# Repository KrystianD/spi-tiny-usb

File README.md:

spi-tiny-usb
============

SPI interface adapter over USB with Linux kernel module.

NOTE: you need to set your custom VID/PID pair for USB device descriptor as I do not provide any.

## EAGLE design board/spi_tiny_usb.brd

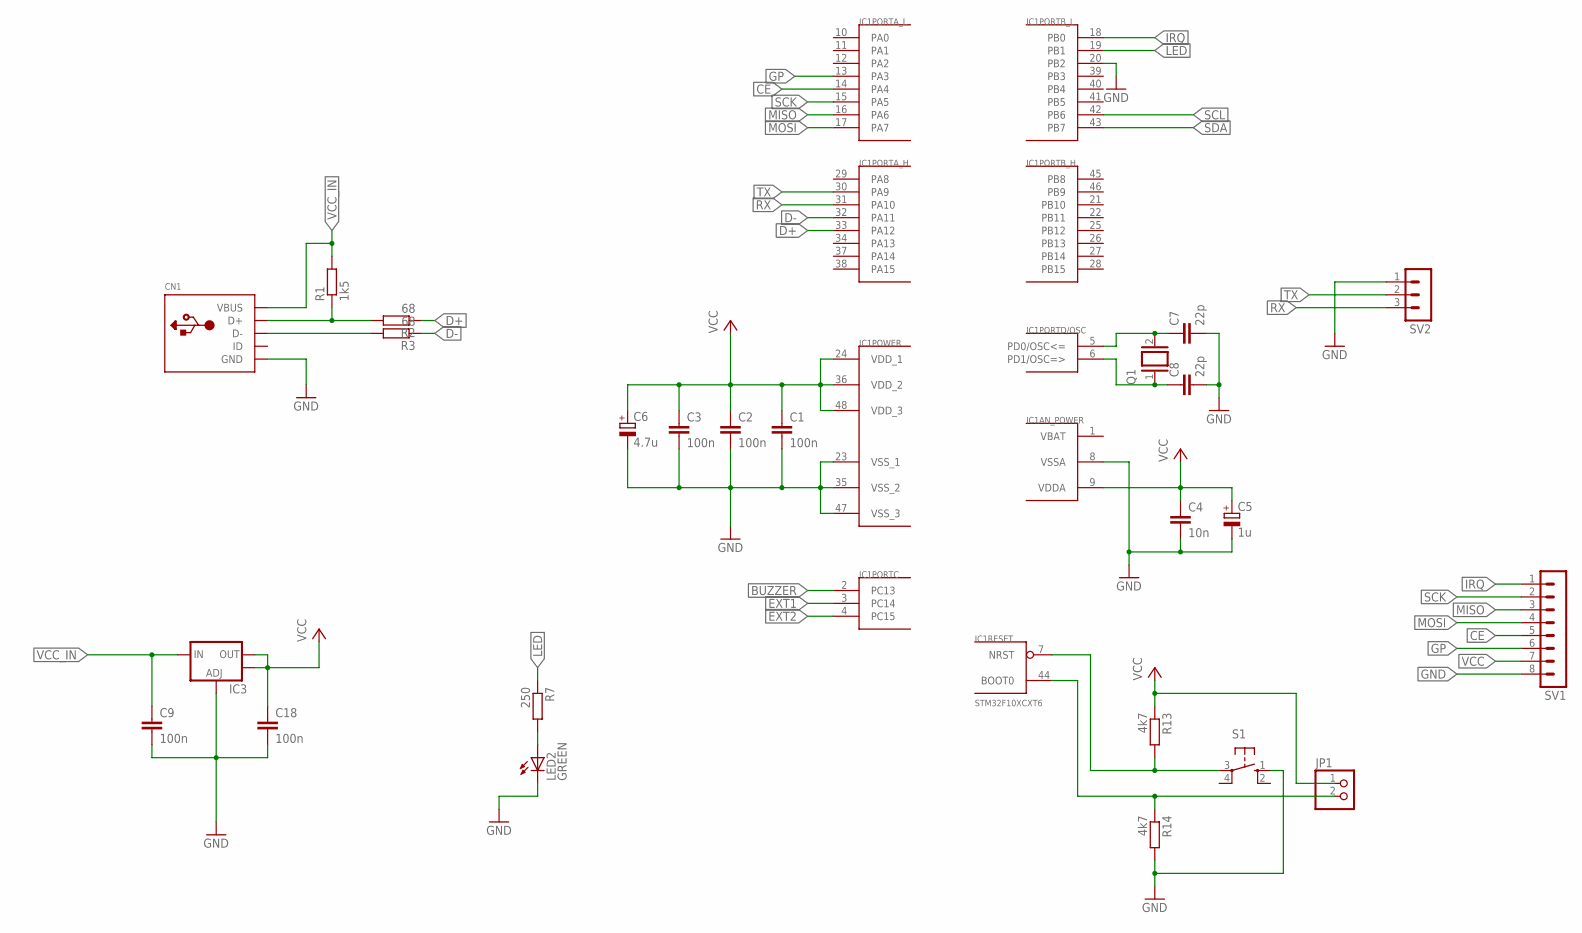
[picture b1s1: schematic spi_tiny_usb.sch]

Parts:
C1, C2, C3, C9, C18: 100n; C0805
C4: 10n; C0805
C5: 1u; 153CLV-0505
C6: 4.7u; 153CLV-0505
C7, C8: 22p; C0805
CN1: USBMINIB; USB-MINIB
IC1: STM32F10XCXT6; TQFP48
IC3: V_REG_LM1117SOT223; SOT223
JP1: PINHD-1X2; 1X02
LED2: GREEN; CHIPLED_0805
Q1: XTAL/S; QS
R1: 1k5; M1206
R2, R3: 68; M0805
R7: 250; R0805
R13: 4k7; R0805
R14: 4k7; R1206
S1: 10-XX; B3F-10XX
SV1: MA08-1
SV2: MA03-1

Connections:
BUZZER: IC1.2 (PC13)
CE: IC1.14 (PA4), SV1.5
D+: IC1.33 (PA12), R2.1
D-: IC1.32 (PA11), R3.1
EXT1: IC1.3 (PC14)
EXT2: IC1.4 (PC15)
GND: C1.2, C2.2, C3.2, C4.2, C5.-, C6.-, C7.2, C8.2, C9.2, C18.2, CN1.GND, IC1.8 (VSSA), IC1.20 (PB2), IC1.23 (VSS_1), IC1.35 (VSS_2), IC1.47 (VSS_3), IC3.1 (ADJ), LED2.C, R14.2, S1.1 (S), SV1.8, SV2.1
GP: IC1.13 (PA3), SV1.6
IRQ: IC1.18 (PB0), SV1.1
LED: IC1.19 (PB1), R7.1
MISO: IC1.16 (PA6), SV1.3
MOSI: IC1.17 (PA7), SV1.4
unnamed: C7.1, IC1.5 (PD0/OSC<=), Q1.2
unnamed: C8.1, IC1.6 (PD1/OSC=>), Q1.1
unnamed: CN1.D+, R1.1, R2.2
unnamed: CN1.D-, R3.2
unnamed: LED2.A, R7.2
unnamed: IC1.44 (BOOT0), JP1.2, R14.1
RST: IC1.7 (NRST), R13.2, S1.3
RX: IC1.31 (PA10), SV2.3
SCK: IC1.15 (PA5), SV1.2
SCL: IC1.42 (PB6)
SDA: IC1.43 (PB7)
TX: IC1.30 (PA9), SV2.2
VBAT: IC1.1 (VBAT)
VCC: C1.1, C2.1, C3.1, C4.1, C5.+, C6.+, C18.1, IC1.9 (VDDA), IC1.24 (VDD_1), IC1.36 (VDD_2), IC1.48 (VDD_3), IC3.2 (OUT), IC3.4 (OUT), JP1.1, R13.1, SV1.7
VCC_IN: C9.1, CN1.VBUS, IC3.3 (IN), R1.2

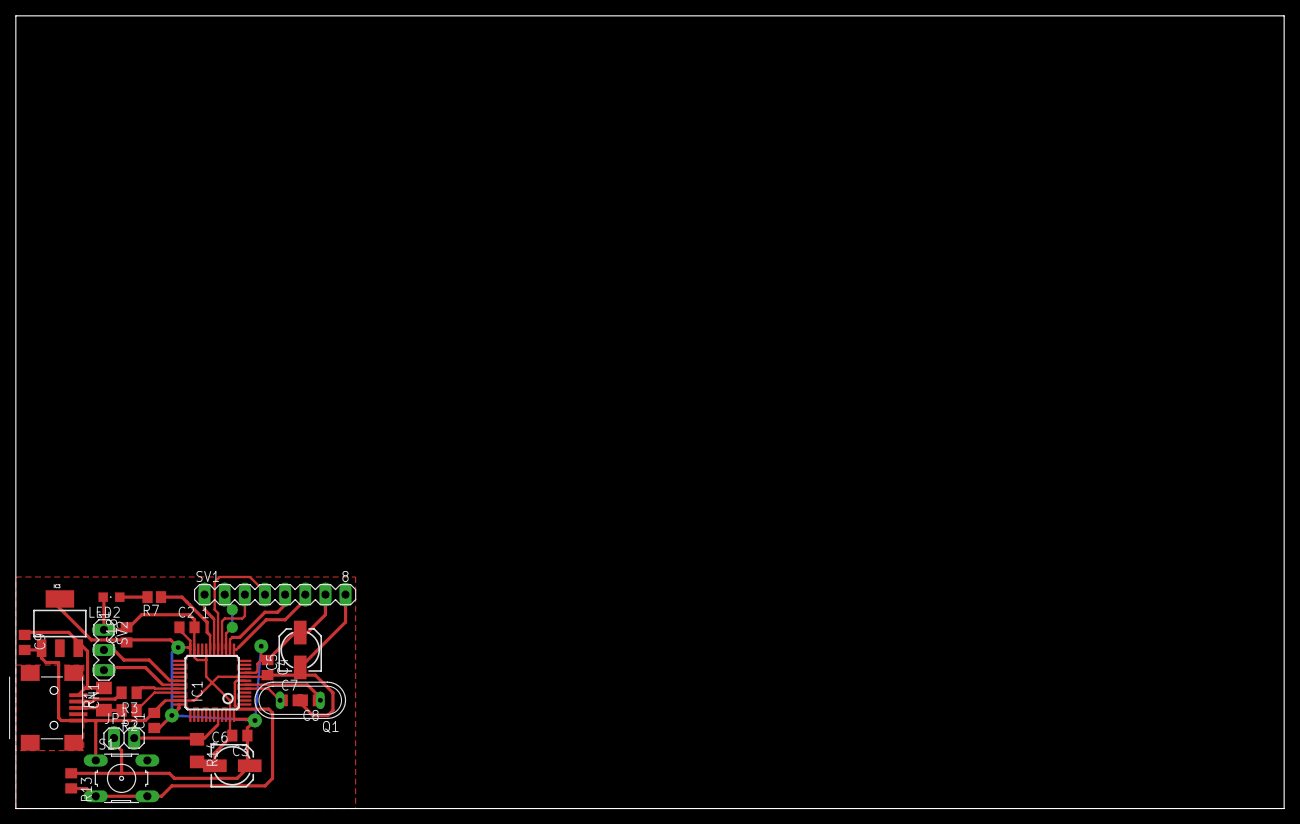
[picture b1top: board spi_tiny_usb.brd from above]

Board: 2 copper layers, 160.0 x 100.0 mm, 25 parts (0 on the bottom side), 21 nets.

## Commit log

2014-06-08 added spi-tiny-usb module based on i2c-tiny-usb
2014-06-08 added registering in filesystem via spidev module
2014-06-09 added stm32 firmware
2014-06-09 added config file fixed module memory allocation for usb transfer
2014-06-09 started interrupt handling
2014-06-09 fixed error handling in probe function added proper chip enable/disable handling
2014-06-09 added clock rate handling removed unused i2c code
2014-06-09 added handling cs_change and delay_usecs of spi_transfer added errors handling in transfer function
2014-06-09 added interrupt handling to firmware
2014-06-09 added interrupt handling to kernel module
2014-06-09 added GPIO interface
2014-06-09 added proper (exported) GPIO removing
2014-06-09 refactor
2014-06-09 devm_spi_register_master changed to spi_register_master for compability with older kernels
2014-06-11 added debug version to Makefile
2014-06-12 added Eagle board and schematic
2021-06-29 typo

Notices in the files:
parts and their libraries:
SparkFun: Licensing: CC v3.0 Share-Alike You are welcome to use this library for commercial purposes.
